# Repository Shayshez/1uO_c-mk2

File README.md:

# 1uO_c-mk2
Version 2 for 1uO_c, include VOR system and front usb

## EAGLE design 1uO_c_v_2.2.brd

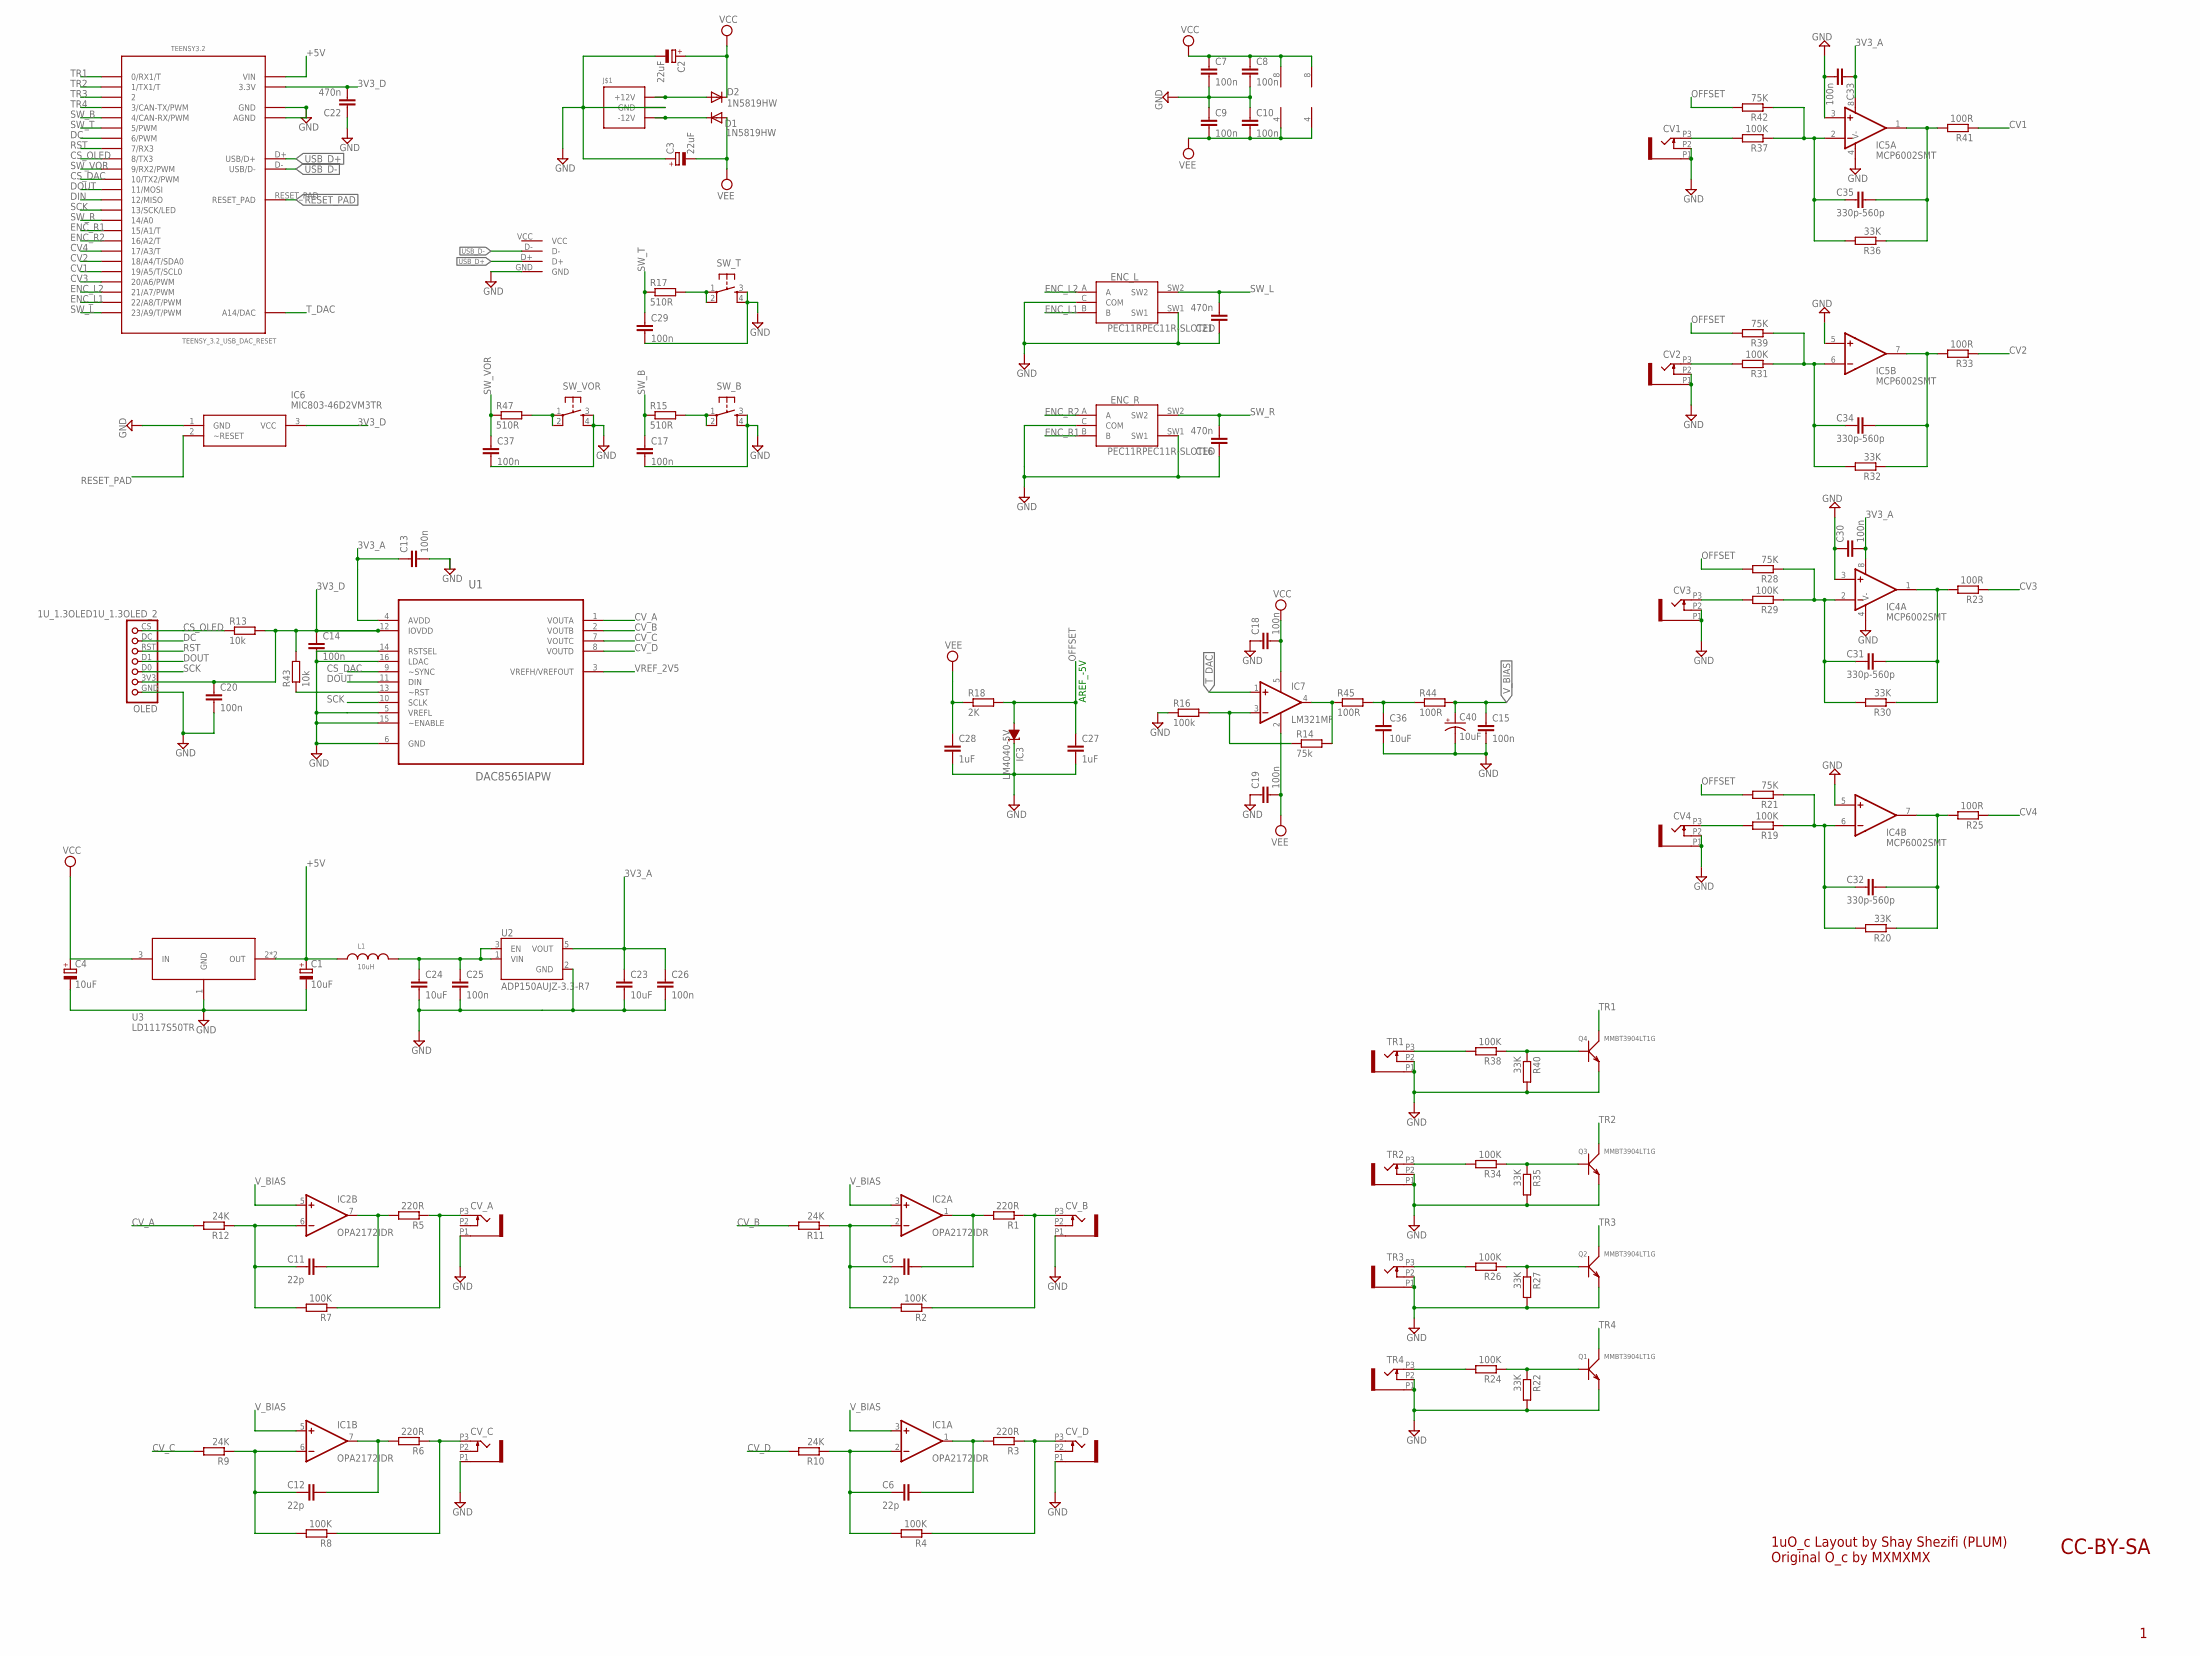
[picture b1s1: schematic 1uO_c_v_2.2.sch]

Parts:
C1, C4: 10uF; PANASONIC_B
C2, C3: 22uF; PANASONIC_C
C5, C6, C11, C12: 22p; C0603
C7, C8, C9, C10, C13, C14, C15, C17, C18, C19, C20, C25, C26, C29, C30, C33, C37: 100n; C0603
C16, C21, C22: 470n; C0603
C23, C24: 10uF; C1206K
C27, C28: 1uF; C0603
C31, C32, C34, C35: 330p-560p; C0603
C36: 10uF; C0603
C40: 10uF; PANASONIC_A
CV1, CV2, CV3, CV4: OG-PJ301_PJ301_THONKICONN; OG-PJ301_WQP_PJ_301M6_NO_HOLE
CV_A: OG-PJ301_PJ301_THONKICONN; OG-PJ301_WQP_PJ_301M6_NO_HOLE
CV_B: OG-PJ301_PJ301_THONKICONN; OG-PJ301_WQP_PJ_301M6_NO_HOLE
CV_C: OG-PJ301_PJ301_THONKICONN; OG-PJ301_WQP_PJ_301M6_NO_HOLE
CV_D: OG-PJ301_PJ301_THONKICONN; OG-PJ301_WQP_PJ_301M6_NO_HOLE
D1, D2: 1N5819HW; DIODE_SOD123
ENC_L: PEC11RPEC11R-SLOTED; PEC11R-SLOTED
ENC_R: PEC11RPEC11R-SLOTED; PEC11R-SLOTED
IC1, IC2: OPA2172IDR; SO08
IC3: LM4040-5V; DBZ_R-PDSO-G3
IC4, IC5: MCP6002SMT; SOIC8
IC6: MIC803-46D2VM3TR; SOT95P230X110-3N
IC7: LM321MF; SOT23-5
J$1: POWER_SIMPLE10; POWER_10
L1: 10uH; WE-LQ_M
OLED: 1U_1.3OLED1U_1.3OLED_2; 1U_1.3OLED_2
Q1, Q2, Q3, Q4: MMBT3904LT1G; SOT-23
R1, R3, R5, R6: 220R; R0603
R2, R4, R7, R8, R19, R24, R26, R29, R31, R34, R37, R38: 100K; R0603
R9, R10, R11, R12: 24K; R0603
R13, R43: 10k; R0603
R14: 75k; R0603
R15, R17, R47: 510R; R0603
R16: 100k; R0603
R18: 2K; R0603
R20, R22, R27, R30, R32, R35, R36, R40: 33K; R0603
R21, R28, R39, R42: 75K; R0603
R23, R25, R33, R41, R44, R45: 100R; R0603
SW_B: TAC_SWITCHPTH; TACTILE-PTH
SW_T: TAC_SWITCHPTH; TACTILE-PTH
SW_VOR: TAC_SWITCHPTH; TACTILE-PTH
TEENSY3.2: TEENSY_3.2_USB_DAC_RESET
TR1, TR2, TR3, TR4: OG-PJ301_PJ301_THONKICONN; OG-PJ301_WQP_PJ_301M6_NO_HOLE
U1: DAC8565IAPW; SOP65P640X120-16N
U2: ADP150AUJZ-3.3-R7; SOT95P280X100-5N
U3: LD1117S50TR; SOT223
U$1: USB_BOARD; MICRO-USB-BOARD

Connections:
3V3_A: C13.1, C23.1, C26.1, C30.2, C33.1, IC4.8 (V+), IC5.8 (V+), U1.4 (AVDD), U2.5 (VOUT)
3V3_D: C14.1, C20.1, C22.2, IC6.3 (VCC), OLED.3V3, R13.2, R43.2, TEENSY3.2.3.3V, U1.12 (IOVDD)
+5V: C1.+, L1.1, TEENSY3.2.VIN, U3.2 (OUT), U3.4 (OUT)
CS_DAC: TEENSY3.2.10 (10/TX2/PWM), U1.9 (~SYNC)
CS_OLED: OLED.CS, R13.1, TEENSY3.2.8 (8/TX3)
CV1: R41.1, TEENSY3.2.19/A5 (19/A5/T/SCL0)
CV2: R33.1, TEENSY3.2.18/A4 (18/A4/T/SDA0)
CV3: R23.1, TEENSY3.2.20/A6 (20/A6/PWM)
CV4: R25.1, TEENSY3.2.17/A3 (17/A3/T)
CV_A: R12.2, U1.1 (VOUTA)
CV_B: R11.2, U1.2 (VOUTB)
CV_C: R9.2, U1.7 (VOUTC)
CV_D: R10.2, U1.8 (VOUTD)
DC: OLED.DC, TEENSY3.2.6 (6/PWM)
DIN: TEENSY3.2.12 (12/MISO)
DOUT: OLED.D1, TEENSY3.2.11 (11/MOSI), U1.11 (DIN)
ENC_L1: ENC_L.B, TEENSY3.2.22/A8 (22/A8/T/PWM)
ENC_L2: ENC_L.A, TEENSY3.2.21/A7 (21/A7/PWM)
ENC_R1: ENC_R.B, TEENSY3.2.15/A1 (15/A1/T)
ENC_R2: ENC_R.A, TEENSY3.2.16/A2 (16/A2/T)
GND: C1.-, C2.-, C3.+, C4.-, C7.2, C8.2, C9.1, C10.1, C13.2, C14.2, C15.2, C16.1, C17.2, C18.1, C19.1, C20.2, C21.1, C22.1, C23.2, C24.2, C25.2, C26.2, C27.2, C28.2, C29.2, C30.1, C33.2, C36.2, C37.2, C40.-, CV1.P1 (1), CV1.P2 (2), CV2.P1 (1), CV2.P2 (2), CV3.P1 (1), CV3.P2 (2), CV4.P1 (1), CV4.P2 (2), CV_A.P1 (1), CV_B.P1 (1), CV_C.P1 (1), CV_D.P1 (1), ENC_L.C (COM), ENC_L.SW1, ENC_R.C (COM), ENC_R.SW1, IC3.1 (C), IC4.3 (+IN), IC4.4 (V-), IC4.5 (+IN), IC5.3 (+IN), IC5.4 (V-), IC5.5 (+IN), IC6.1 (GND), J$1.3 (GND), J$1.4 (GND), J$1.5 (GND), J$1.6 (GND), J$1.7 (GND), J$1.8 (GND), OLED.GND, Q1.2 (E), Q2.2 (E), Q3.2 (E), Q4.2 (E), R16.1, R22.2, R27.2, R35.2, R40.2, SW_B.3, SW_B.4, SW_T.3, SW_T.4, SW_VOR.3, SW_VOR.4, TEENSY3.2.AGND, TEENSY3.2.GND, TR1.P1 (1), TR1.P2 (2), TR2.P1 (1), TR2.P2 (2), TR3.P1 (1), TR3.P2 (2), TR4.P1 (1), TR4.P2 (2), U1.5 (VREFL), U1.6 (GND), U1.14 (RSTSEL), U1.15 (~ENABLE), U1.16 (LDAC), U2.2 (GND), U3.1 (GND), U$1.GND
unnamed: D1.C, J$1.1 (-12V), J$1.2 (-12V)
unnamed: D2.A, J$1.9 (+12V), J$1.10 (+12V)
unnamed: C24.1, C25.1, L1.2, U2.1 (VIN), U2.3 (EN)
unnamed: CV1.P3 (3), R37.2
unnamed: C35.2, IC5.2 (-IN), R36.2, R37.1, R42.1
unnamed: C35.1, IC5.1 (OUT), R36.1, R41.2
unnamed: R17.2, SW_T.1, SW_T.2
unnamed: CV2.P3 (3), R31.2
unnamed: R15.2, SW_B.1, SW_B.2
unnamed: C34.2, IC5.6 (-IN), R31.1, R32.2, R39.1
unnamed: C34.1, IC5.7 (OUT), R32.1, R33.2
unnamed: CV3.P3 (3), R29.2
unnamed: C31.2, IC4.2 (-IN), R28.1, R29.1, R30.2
unnamed: C31.1, IC4.1 (OUT), R23.2, R30.1
unnamed: CV4.P3 (3), R19.2
unnamed: C32.2, IC4.6 (-IN), R19.1, R20.2, R21.1
unnamed: C32.1, IC4.7 (OUT), R20.1, R25.2
unnamed: R38.2, TR1.P3 (3)
unnamed: Q4.1 (B), R38.1, R40.1
unnamed: R34.2, TR2.P3 (3)
unnamed: Q3.1 (B), R34.1, R35.1
unnamed: R26.2, TR3.P3 (3)
unnamed: Q2.1 (B), R26.1, R27.1
unnamed: R24.2, TR4.P3 (3)
unnamed: Q1.1 (B), R22.1, R24.1
unnamed: C5.2, IC2.2 (-IN), R2.2, R11.1
unnamed: C11.2, IC2.6 (-IN), R7.2, R12.1
unnamed: C11.1, IC2.7 (OUT), R5.2
unnamed: CV_A.P3 (3), R5.1, R7.1
unnamed: C5.1, IC2.1 (OUT), R1.2
unnamed: CV_B.P3 (3), R1.1, R2.1
unnamed: C12.2, IC1.6 (-IN), R8.2, R9.1
unnamed: C12.1, IC1.7 (OUT), R6.2
unnamed: CV_C.P3 (3), R6.1, R8.1
unnamed: C6.2, IC1.2 (-IN), R4.2, R10.1
unnamed: C6.1, IC1.1 (OUT), R3.2
unnamed: CV_D.P3 (3), R3.1, R4.1
unnamed: R43.1, U1.13 (~RST)
unnamed: IC7.3 (-IN), R14.1, R16.2
unnamed: IC7.4 (OUT), R14.2, R45.1
unnamed: C36.1, R44.1, R45.2
unnamed: R47.2, SW_VOR.1, SW_VOR.2
OFFSET: C27.1, IC3.2 (A), R18.2, R21.2, R28.2, R39.2, R42.2
RESET_PAD: IC6.2 (~RESET), TEENSY3.2.RESET_PAD
RST: OLED.RST, TEENSY3.2.7 (7/RX3)
SCK: OLED.D0, TEENSY3.2.13 (13/SCK/LED), U1.10 (SCLK)
SW_B: C17.1, R15.1, TEENSY3.2.4 (4/CAN-RX/PWM)
SW_L: C21.2, ENC_L.SW2, TEENSY3.2.23/A9 (23/A9/T/PWM)
SW_R: C16.2, ENC_R.SW2, TEENSY3.2.14/A0
SW_T: C29.1, R17.1, TEENSY3.2.5 (5/PWM)
SW_VOR: C37.1, R47.1, TEENSY3.2.9 (9/RX2/PWM)
TR1: Q4.3 (C), TEENSY3.2.0 (0/RX1/T)
TR2: Q3.3 (C), TEENSY3.2.1 (1/TX1/T)
TR3: Q2.3 (C), TEENSY3.2.2
TR4: Q1.3 (C), TEENSY3.2.3 (3/CAN-TX/PWM)
T_DAC: IC7.1 (+IN), TEENSY3.2.RESET/DAC (A14/DAC)
USB_D+: TEENSY3.2.D+ (USB/D+), U$1.D+
USB_D-: TEENSY3.2.D- (USB/D-), U$1.D-
VCC: C2.+, C4.+, C7.1, C8.1, C18.2, D2.C, IC1.8 (V+), IC2.8 (V+), IC7.5 (V+), U3.3 (IN)
VEE: C3.-, C9.2, C10.2, C19.2, C28.1, D1.A, IC1.4 (V-), IC2.4 (V-), IC7.2 (V-), R18.1
VREF_2V5: U1.3 (VREFH/VREFOUT)
V_BIAS: C15.1, C40.+, IC1.3 (+IN), IC1.5 (+IN), IC2.3 (+IN), IC2.5 (+IN), R44.2

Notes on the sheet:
AREF_-5V
1uO_c Layout by Shay Shezifi (PLUM) Original O_c by MXMXMX
CC-BY-SA

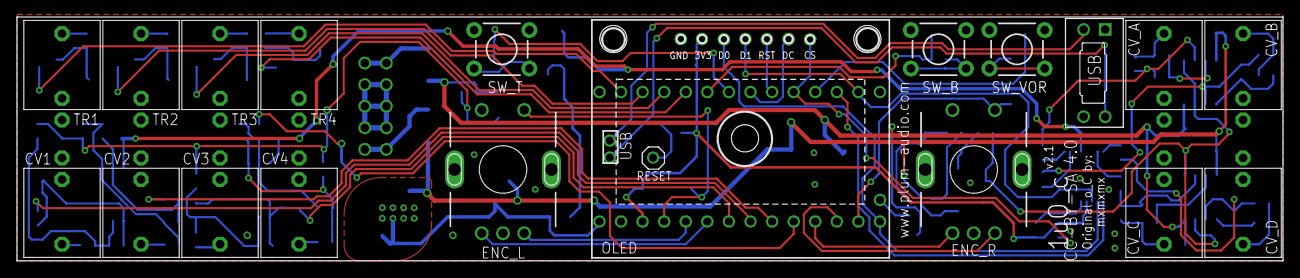
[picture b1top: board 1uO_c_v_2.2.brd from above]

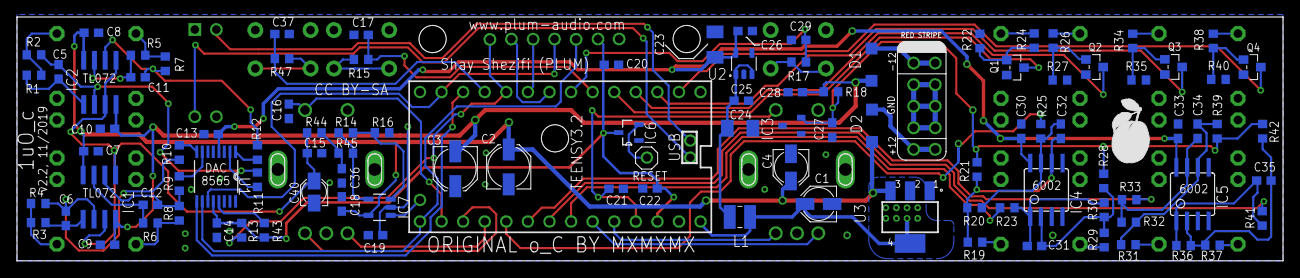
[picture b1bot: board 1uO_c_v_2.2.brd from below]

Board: 2 copper layers, 149.0 x 28.7 mm, 122 parts (103 on the bottom side), 81 nets.

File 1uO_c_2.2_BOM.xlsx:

Qty | Value | Device | Package | Parts | Description | MOUSER_PART_NUMBER | ARROW_PRICE-STOCK | AVAILABILITY | DESCRIPTION | HEIGHT | MANUFACTURER_NAME | MANUFACTURER_PART_NUMBER | MF | MP | MPN | PACKAGE | PRICE | RS_PART_NUMBER | RS_PRICE-STOCK | SPICEPREFIX | VALUE | WE-NUMBER
 | Resistors 0603 1% |  |  |  |  | 603-RC0603FR-07100RL
6 | 100R | R-EU_R0603 | R0603 | R23, R25, R33, R41, R44, R45 | RESISTOR, European symbol | 603-RC0603FR-07220RL |  |  |  |  |  |  |  |  |  |  |  |  |  | R
4 | 220R | R-EU_R0603 | R0603 | R1, R3, R5, R6 | RESISTOR, European symbol | 603-RC0603FR-07510RL |  |  |  |  |  |  |  |  |  |  |  |  |  | R
3 | 510R | R-EU_R0603 | R0603 | R15, R17, R47 | RESISTOR, European symbol | 603-RC0603FR-102KL |  |  |  |  |  |  |  |  |  |  |  |  |  | R
1 | 2K | R-EU_R0603 | R0603 | R18 | RESISTOR, European symbol | 603-RC0603FR-0710KL |  |  |  |  |  |  |  |  |  |  |  |  |  | R
2 | 10k | R-EU_R0603 | R0603 | R13, R43 | RESISTOR, European symbol | 603-RC0603FR-0724K9L |  |  |  |  |  |  |  |  |  |  |  |  |  | R
4 | 24K | R-EU_R0603 | R0603 | R9, R10, R11, R12 | RESISTOR, European symbol | 603-RC0603FR-1333KL |  |  |  |  |  |  |  |  |  |  |  |  |  | R
8 | 33K | R-EU_R0603 | R0603 | R20, R22, R27, R30, R32, R35, R36, R40 | RESISTOR, European symbol | 603-RC0603FR-0747KL |  |  |  |  |  |  |  |  |  |  |  |  |  | R
5 | 75K | R-EU_R0603 | R0603 | R14, R21, R28, R39, R42 | RESISTOR, European symbol | 603-AC0603FR-0775KL |  |  |  |  |  |  |  |  |  |  |  |  |  | R
13 | 100K | R-EU_R0603 | R0603 | R2, R4, R7, R8, R16, R19, R24, R26, R29, R31, R34, R37, R38 | RESISTOR, European symbol | 603-RC0603FR-07100KL |  |  |  |  |  |  |  |  |  |  |  |  |  | R
 | Caps MLCC
4 | 22p | C-EUC0603 | C0603 | C5, C6, C11, C12 | CAPACITOR, European symbol | 80-C0603C220J5G7411
4 | 560p | C-EUC0603 | C0603 | C31, C32, C34, C35 | CAPACITOR, European symbol | 581-06035A561G
17 | 100n | C-EUC0603 | C0603 | C7, C8, C9, C10, C13, C14, C15, C17, C18, C19, C20, C25, C26, C29, C30, C33, C37 | CAPACITOR, European symbol | 80-C0603C104K3NAUTO
3 | 470n | C-EUC0603 | C0603 | C16, C21, C22 | CAPACITOR, European symbol | 963-UMK107B7474KA-TR
2 | 1uF | C-EUC0603 | C0603 | C27, C28 | CAPACITOR, European symbol | 603-CC603KRX5R8BB105
1 | 10uF | C-EUC0603 | C0603 | C36 | CAPACITOR, European symbol | 963-LMK107BBJ106KALT
2 | 10uF | C-EUC1206K | C1206K | C23, C24 | CAPACITOR, European symbol | 963-TMK316BJ106ML-T
 | Caps Electrolytics
2 | 10uF | CPOL-EUB | PANASONIC_B | C1, C4 | POLARIZED CAPACITOR, European symbol | 667-EEE-FK1H100SR |  |  |  |  |  |  |  |  |  |  |  |  |  | C
1 | 10uF | CPOL-USA | PANASONIC_A | C40 | POLARIZED CAPACITOR, American symbol | 647-UWX1C100MCL2
2 | 22uF | CPOL-EUC | PANASONIC_C | C2, C3 | POLARIZED CAPACITOR, European symbol | 667-EEE-FK1H220SR |  |  |  |  |  |  |  |  |  |  |  |  |  | C
 | Inductor
1 | 10uH | WE-LQ_1210_744032001 | WE-LQ_M | L1 | SMD Inductor | 963-LB3218T100K |  |  |  |  |  |  |  |  |  |  |  |  |  |  |  | 744032001/1uH
 | Chips
2 | 1N5819HW | DIODE_DIODE-SOD123 | DIODE_SOD123 | D1, D2 | DIODE | 621-1N5819HW-F
1 | ADP150AUJZ-3.3-R7 | ADP150AUJZ-3.3-R7 | SOT95P280X100-5N | U2 | IC REG LINEAR 2V 150MA 5TSOT | 584-ADP150AUJZ-3.3R7 |  | Good | LDO Regulator Pos 2V 0.15A 5-Pin TSOT T/R |  |  |  | Analog Devices | ADP150AUJZ-2.0-R7 |  | TSOT-23 Analog Devices | 0.65 USD
1 | DAC8565IAPW | DAC8565IAPW | SOP65P640X120-16N | U1 | Quad Channel DAC | 595-DAC8565IAPW |  | Good | 16-Bit, Quad Channel, Ultra-Low Glitch, Voltage Output DAC with 2.5V, 2ppm/C In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 |  |  |  | Texas Instruments | DAC8565IAPW |  | TSSOP-16 Texas Instruments | 10.78 USD
1 | LD1117S50TR | LD1117S50TR | SOT223 | U3 | http://octopart.com/ld1117s50tr-stmicroelectronics-529395 | 511-LD1117S50 |  | Good | LD1117 Series 1300 mA 5 V Fixed Output Positive Voltage LDO Regulator - SOT-223 |  |  |  | STMicroelectronics | LD1117S50TR |  | SOT-223 STMicroelectronics | 0.19 USD
1 | LM321MF | LM321MF | SOT23-5 | IC7 | Low Power Single Op Amp | LM321MF/NOPB
1 | LM4040-5V | LM4041B12DBZ | DBZ_R-PDSO-G3 | IC3 | PRECISION MICROPOWER SHUNT VOLTAGE REFERENCE | 926-LM4040DIM350NOPB
2 | MCP6002SMT | MCP6002SMT | SOIC8 | IC4, IC5 | Dual General Op Amp | 579-MCP6002T-I/SN
1 | MIC803-46D2VM3TR | MIC803-46D2VM3TR | SOT95P230X110-3N | IC6 | 3-pin Microprocessor Supervosor Circui | MIC803-46D2VM3TR |  |  | 3-pin Microprocessor Supervosor Circui | mm | Micrel | MIC803-46D2VM3TR
4 | MMBT3904LT1G | SMD-TRANSISTORS-NPN-40V-200MA-MMBT3904LT1G(SOT-23) | SOT-23 | Q1, Q2, Q3, Q4 | 305010013 | 863-MMBT3904LT1G |  |  |  |  |  |  |  |  | MMBT3904LT1G |  |  |  |  |  | MMBT3904LT1G
2 | TL072 | TL072D | SO08 | IC1, IC2 | OP AMP | 595-TL072CDR
 | Misc
1 | 1X40 Pin Header | Theensy / OLED connector
1 | POWER HEADER 10 PINS | Pin headers 2.54mm 2X5 | POWER | J$1
2 | PEC11RPEC11R | PEC11RPEC11R | PEC11R | ENC_L, ENC_R | Incremental encoder 24 detents 24 pulses Bourns 24 Pulse Incremental Mechanical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 | 858-EN11-HSM1BF20
1 | TEENSY_3.2_USB_DAC_RESET | TEENSY_3.2_USB_DAC_RESET | TEENSY_3.2_USB_DAC_RESET | TEENSY3.2 |  | DEV-13736
1 | USB_BOARD | USB_BOARD | MICRO-USB-BOARD | U$1
1 | USB Connector | USB Connector Type B micro, VERT - DIP | Wurth Elektronik 614105150621 | Wurth Elektronik 614105150621 | USB Connectors WR-COM USB Micro THT Type AB Vertical | 710-614105150621
3 |  | TACT Switches | E-switch TL1105SPF250Q | SW_B, SW_T, SW_VOR | Momentary Switch | 612-TL1105SP-250
3 |  | TACT Switches caps | E-switch 1RBLK | SW_B, SW_T, SW_VOR |  | 12-1R-BK
1 | Plum 1U_1.3OLED_2 | Plum 1U_1.3OLED_2 |  | OLED | https://github.com/Shayshez/1_3_OLED_FOR_1U
1 | OLED SCREEN |  |  |  | https://github.com/Shayshez/1_3_OLED_FOR_1U
12 | PJ301_THONKICONN | PJ301_THONKICONN | WQP_PJ_301M | CV1, CV2, CV3, CV4, CV_A, CV_B, CV_C, CV_D, TR1, TR2, TR3, TR4

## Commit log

2020-06-28 Mouser part numbers update

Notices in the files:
1uO_c_v_2.2.brd:
CC-BY-SA 4.0
parts and their libraries:
Wurth_Elektronik_Passive_rev17b: Copyright: Würth Elektronik
